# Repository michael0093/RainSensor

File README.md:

# RainSensor
Anti-Corrosion Rain Sensor

## Overview
Unlike the cheap rain sensors that corrode quickly this design uses a small AC signal to detect rain either resistively or capacitively. The AC signal is small enough to be below the voltage required for electrochemical corrosion thereby extending the sensor life considerably. 

In addition, this design features both analog and digital outputs and can operate from 3.3V or 5V. The on-board heater can also operate automatically when moisture is detected, or manually via a control pin.

## Pin Description
| Nbr | Name    | Description 			| Specifications														|
| --- | -------	| --------------------- | --------------------------------------------------------------------- |
|  1  | HTR+ 	| Heater supply voltage | 5V input = 2W heater, 3.3V = 0.9W. 5V max								|
|  2  | GND  	| Ground 0V  			| Common 0V but intended mainly for heater current						|
|  3  | Heat  	| Heater control input	| 0V/open=off 3.3V-5V=on. In auto-heat mode can be used to read DigOut	|
|  4  | VDD  	| Logic supply voltage	| 3.3V-5V input. Typical current consumption 5-8mA					|
|  5  | GND  	| Ground 0V  			| Common 0V but intended mainly for logic voltage						|
|  6  | DigOut  | Digital output  		| 0V=no rain, VDD=rain. Recommend <5mA draw. Adjustable threshold.		|
|  7  | AnaOut	| Analog output			| 0V=no rain, VDD=rain. Recommend <5mA draw. Adjustable gain.			|

## Setup and Configuration Options
1. First decide if the Auto-Heat option is desired - refer to the last section of "Circuit Description" below. To enable auto heat, bridge jumper JP1, otherwise leave it open (default) to disable auto heat. 
2. Next, power up the board with the desired VDD (3.3V to 5V).

For resistive sensing mode follow the numbered steps below. Capacitive sensing mode is more durable but less sensitive - if this is desired then first cover the entire sensing area in a thin plastic tape (such as clear packaging tape) then follow the same steps below. The thinner the tape the better the sensitivity.

3. For analog output, cover the sensor element with some al-foil or other conductive material. In capacitive mode, make sure it is pressed against the sensor but do not touch it with your hands whilst adjusting the trimpots as that will affect the measurement.
4. Adjust the gain trimpot all the way counter clockwise (min gain) then slowly clockwise until the AnaOut voltage reaches the maximum ADC input voltage for your system. For example most ESP32 boards have a 1V ADC input maximum. The sensor is now ready for use.
5. For digital output use, remove the conductive material and instead apply a few drops of water. Adjust the DigOut Thresh trimpot until the orange LED lights to indicate moisture is detected. Then reduce the threshold very slightly (counter-clockwise) to give a little margin on the threshold point.
6. Install your sensor in a waterproof case and position it in an open area, angled to allow rain to slide off it preferably with the points of the sensor element pointing downwards.

## Circuit Description
Opamp U1A is configured as a relaxation oscillator with a frequency of about 6-8kHz. R5 and D1 on the output clamp the voltage to about 0.5Vpp independent of the supply voltage. This passes through C3 to make it AC-coupled into the rain sensor element. R6 and R7 keep the sensor biased around 0V. Opamp U1B is a precision rectifier configuration with gain set by RV2, and its frequency response is shaped to reject 50Hz and provide peak gain at the ~8kHz oscillator frequency. The opamp charges C5 which holds the peak voltage which is then buffered by U1C for the analog output. The digital output is handled by opamp U1D in comparator configuration with hysteresis set by R11/R10 and threshold set by RV1. 

The analog and digital outputs have 100R protection resistors near the connector which limits the practical output current to 5-10mA, however changing this resistor for 0R should provide more (limited by the opamp capabilities). 
The opamp selection is not that critical: anything capable of 3.3-5V operation, with rail-to-rail output, input bias current measured in nA, and GBWP > 500k should do. None of the other parts have any special requirements except perhaps to say that any replacement for Q1 should have similarly low gate votlage and RDson, rated at at least 1A continuous.

The LEDs are a considerable current consumer in the design and could be removed to get the current consumption down to about 4mA. If using high efficiency LEDs and a dim brightness is desired, R9=100k and R12=10k works well.

You may notice that the analog output varies by around 0.1V when the digital output changes between on and off. The reason is that oscillator U1A is slightly infleucned by U1D operating as a comparator both due to U1D's current output and the fact that it is an opamp and not ideally suited for this role. To eliminate the effect, set the DigOut thresh all the way to maximum so the LED is off and always stays off. To minimise the effect whilst still keeping the digital output, reduce R12 to a larger value such as 10k, or remove it completely if you don't need the LED.

The heater is a string of 100R 1206 resistors controlled by an N MOSFET. With the "Auto Heat" jumper open (disabled) the Heat pin controls the heater state directly. When the "Auto Heat" jumper is bridged (enabled) this connects the MOSFET to the digital output signal so that when moisture is detected the heater turns on automatically. In this configuration the Heat pin actually has several functions:
 - For pure auto-heat operation, leave the Heat pin open or connected to an input pin.
 - The Heat pin will copy the state of the DigOut pin, meaning the Heat pin can be read instead of having to run another wire for DigOut and Heat pins.
 - Driving the Heat pin high or low at any time will enable or disable the heater function, thereby over-riding the automatic behaviour.

## Modifications required for Rev A
The latest schematic includes component value changes from testing, as well as a modification that require some PCB track cutting, these changes are highlighted red on the schematic and included below as changes for the next revision.
- 

## Future changes for Rev B
The modifications required for Rev A above, plus these less-important changes to improve circuit performance/robustness:
- Polarity protection at input
- Optional position for resistor divider at digital output (to allow 3.3V logic with 5V power source): better than adjusting gain trimpot
- Low-pass filter at U1B input: 
- Look to commonise the two trimpot values to 500k
- Consider a better solution for the gain trimpot since it is either 100k-150k for resistive sense mode or 500k for capacitive sense mode
- Consider if sensor element can have more capacitive coupling (closer spacing?)

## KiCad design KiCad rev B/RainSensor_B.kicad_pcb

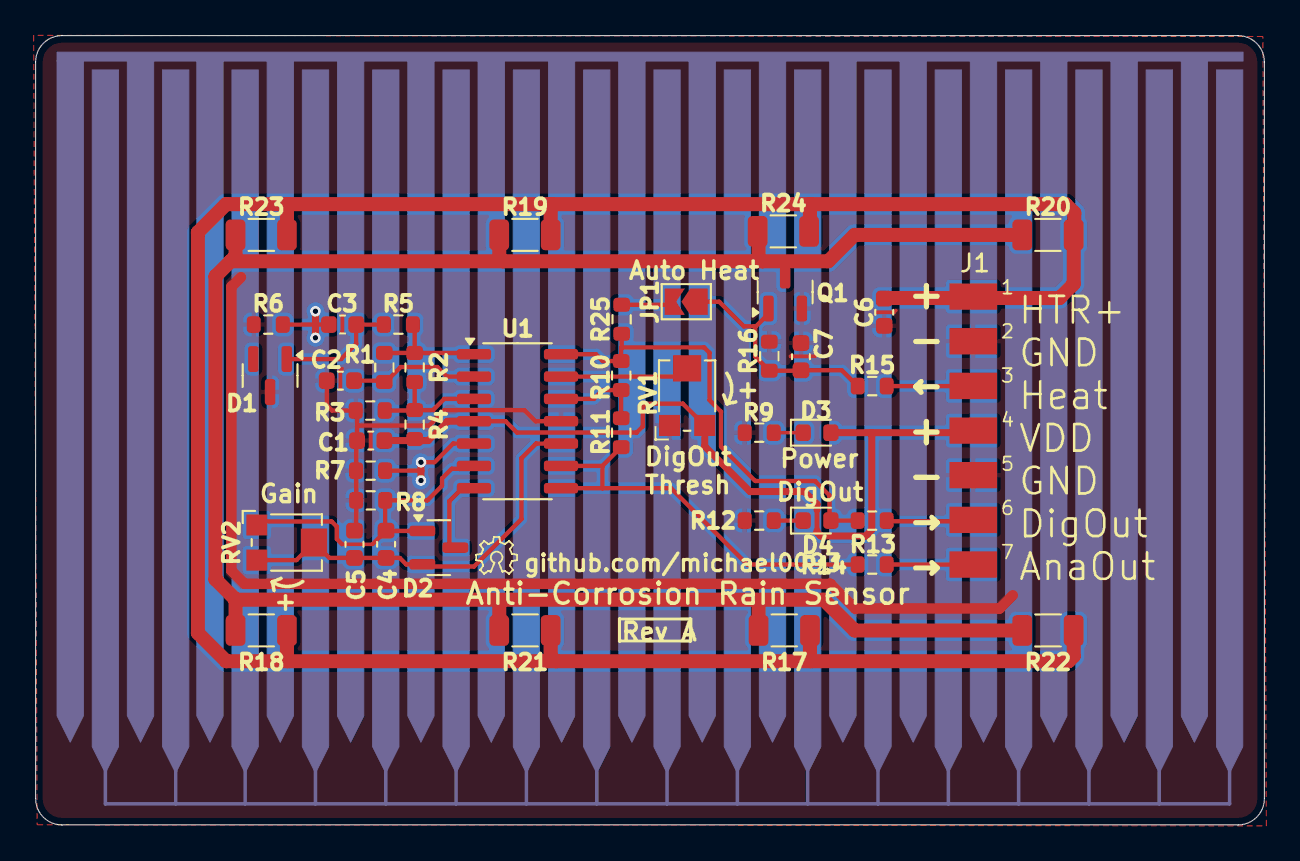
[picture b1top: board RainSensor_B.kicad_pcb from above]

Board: 2 copper layers, 69.9 x 44.9 mm, 42 parts (0 on the bottom side), 24 nets.

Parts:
C1, C2, C3, C4, C5, C6, C7: 100nF; C_0603_1608Metric
D1: BAV99; SOT-23
D2: BAT54S; SOT-23
D3: GREEN; LED_0603_1608Metric
D4: ORANGE; LED_0603_1608Metric
J1: Conn_01x07_Pin; Harwin_M20-89007xx_1x07_P2.54mm_Horizontal_NoSilkscreen
JP1: Auto Heat; SolderJumper-2_P1.3mm_Open_TrianglePad1.0x1.5mm
Q1: AO3400A; SOT-23
R1, R5, R12, R15: 1k; R_0603_1608Metric
R2, R3, R4, R8, R9, R11, R25: 10k; R_0603_1608Metric
R6: 1M; R_0603_1608Metric
R7, R10, R16: 100k; R_0603_1608Metric
R13, R14: 100R; R_0603_1608Metric
R17, R18, R19, R20, R21, R22, R23, R24: 100R; R_1206_3216Metric
RV1: 10k; Potentiometer_Bourns_TC33X_Vertical
RV2: 500k; Potentiometer_Bourns_TC33X_Vertical
U1: LMV324; SOIC-14_3.9x8.7mm_P1.27mm

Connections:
/AnalogOut: R11.1, R14.2, U1.8, U1.9 (-)
/DigitalOut: D4.2 (A), R10.2, R13.2, R25.2, U1.14
/HeaterOn: J1.3, R15.2
GND: C1.2, C2.2, C5.2, C6.2, C7.1, D1.3 (K), J1.2, J1.5, Q1.2 (S), R3.2, R6.1, R7.1, R8.1, R9.2, R12.2, R16.1, RV1.1, U1.11 (V-)
HTR+: C6.1, J1.1, R17.2, R18.2, R19.2, R20.2, R21.2, R22.2, R23.2, R24.2
unnamed: C3.1, D1.1 (K), R5.2
unnamed: C3.2, R6.2
unnamed: C4.1, D2.1 (A), R8.2, RV2.1, U1.6 (-)
unnamed: D2.3 (COM), U1.7
unnamed: C4.2, C5.1, D2.2 (K), RV2.2, RV2.3, U1.10 (+)
unnamed: D3.1 (K), R9.1
unnamed: D4.1 (K), R12.1
unnamed: J1.6, R13.1
unnamed: J1.7, R14.1
unnamed: C7.2, JP1.1 (A), Q1.1 (G), R15.1, R16.2
unnamed: JP1.2 (B), R25.1
unnamed: Q1.3 (D), R17.1, R18.1, R19.1, R20.1, R21.1, R22.1, R23.1, R24.1
unnamed: R1.1, R2.1, R5.1, U1.1
unnamed: R2.2, R3.1, R4.1, U1.3 (+)
unnamed: C2.1, R1.2, U1.2 (-)
unnamed: R7.2, U1.5 (+)
unnamed: R10.1, R11.2, U1.12 (+)
unnamed: RV1.2, U1.13 (-)
VDD: C1.1, D3.2 (A), J1.4, R4.2, RV1.3, U1.4 (V+)

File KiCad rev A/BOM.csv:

Reference,Value,Footprint,Qty,DNP
C1 C2 C3 C4 C5 C6 C7,100nF,Capacitor_SMD:C_0603_1608Metric,7,
Cmod1,1nF,Capacitor_SMD:C_0603_1608Metric,1,
D1,BAV99,Package_TO_SOT_SMD:SOT-23,1,
D2,BAT54S,Package_TO_SOT_SMD:SOT-23,1,
D3,GREEN,LED_SMD:LED_0603_1608Metric,1,
D4,ORANGE,LED_SMD:LED_0603_1608Metric,1,
J1,Conn_01x07_Pin,Connector_Harwin:Harwin_M20-89007xx_1x07_P2.54mm_Horizontal,1,
Q1,AO3400A,Package_TO_SOT_SMD:SOT-23,1,
R1 R5 R12 R15,1k,Resistor_SMD:R_0603_1608Metric,4,
R2 R3 R4 R8 R9 R11 R25,10k,Resistor_SMD:R_0603_1608Metric,7,
R6,1M,Resistor_SMD:R_0603_1608Metric,1,
R7 R10 R16,100k,Resistor_SMD:R_0603_1608Metric,3,
R13 R14,100R,Resistor_SMD:R_0603_1608Metric,2,
R17 R18 R19 R20 R21 R22 R23 R24,100R,Resistor_SMD:R_1206_3216Metric,8,
RV1,10k,Potentiometer_SMD:Potentiometer_Bourns_TC33X_Vertical,1,
RV2,500k,Potentiometer_SMD:Potentiometer_Bourns_TC33X_Vertical,1,
U1,LMV324,Package_SO:SOIC-14_3.9x8.7mm_P1.27mm,1,

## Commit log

2024-09-28 First commit, with 29/06/2024 schematic as originally designed before any modifications.
2024-11-12 Add rev B Kicad project, schematic updated.
